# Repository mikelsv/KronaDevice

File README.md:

# KronaDevice
Krona device. StepUp dc-dc converter from 3.7v to 9v. For tester DT830.

## Sources
KiCad sheme: /StepUp 3_7 to 9 MC34063

### OpenScad source:
/openscad/KronaDevice/StepUp MC34063 3_7 to 9v.scad -- Version 1.1 (11.12.2023) 

### Thingiverse models: 
https://www.thingiverse.com/thing:6368927

## Links
YouTube: https://www.youtube.com/watch?v=WVIPYxtIsH8

Pikabu: ???

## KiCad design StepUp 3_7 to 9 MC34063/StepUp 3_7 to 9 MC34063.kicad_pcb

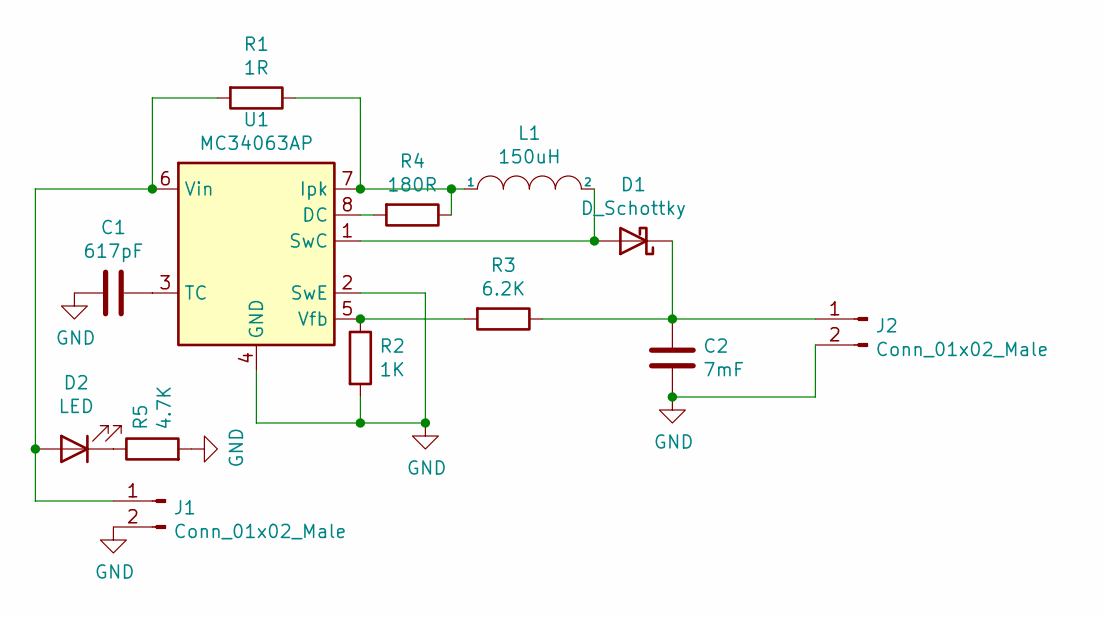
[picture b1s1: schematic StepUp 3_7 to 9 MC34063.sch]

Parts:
C1: 617pF; CP_Radial_Tantal_D4.5mm_P2.50mm
C2: 7mF; CP_Radial_Tantal_D4.5mm_P2.50mm
D1: D_Schottky; R_Axial_DIN0207_L6.3mm_D2.5mm_P10.16mm_Horizontal
D2: LED; LED_D3.0mm
J1, J2: Conn_01x02_Male; PinHeader_1x02_P2.54mm_Vertical
L1: 150uH; R_Axial_DIN0207_L6.3mm_D2.5mm_P10.16mm_Horizontal
R1: 1R; R_Axial_DIN0207_L6.3mm_D2.5mm_P2.54mm_Vertical
R2: 1K; R_Axial_DIN0207_L6.3mm_D2.5mm_P7.62mm_Horizontal
R3: 6.2K; R_Axial_DIN0207_L6.3mm_D2.5mm_P10.16mm_Horizontal
R4: 180R; R_Axial_DIN0207_L6.3mm_D2.5mm_P2.54mm_Vertical
R5: 4.7K; R_Axial_DIN0207_L6.3mm_D2.5mm_P7.62mm_Horizontal
U1: MC34063AP; DIP-8_W7.62mm

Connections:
GND: C1.1, C2.2, J1.2, J2.2, R2.2, R5.2, U1.2 (SwE), U1.4 (GND)
unnamed: C1.2, U1.3 (TC)
unnamed: C2.1, D1.1 (K), J2.1, R3.1
unnamed: D1.2 (A), L1.2, U1.1 (SwC)
unnamed: D2.1 (K), R5.1
unnamed: D2.2 (A), J1.1, R1.2, U1.6 (Vin)
unnamed: L1.1, R1.1, R4.1, U1.7 (Ipk)
unnamed: R2.1, R3.2, U1.5 (Vfb)
unnamed: R4.2, U1.8 (DC)

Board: 2 copper layers, 13 parts (0 on the bottom side), 9 nets, no tracks yet.

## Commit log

2023-12-11 Insert sources.
